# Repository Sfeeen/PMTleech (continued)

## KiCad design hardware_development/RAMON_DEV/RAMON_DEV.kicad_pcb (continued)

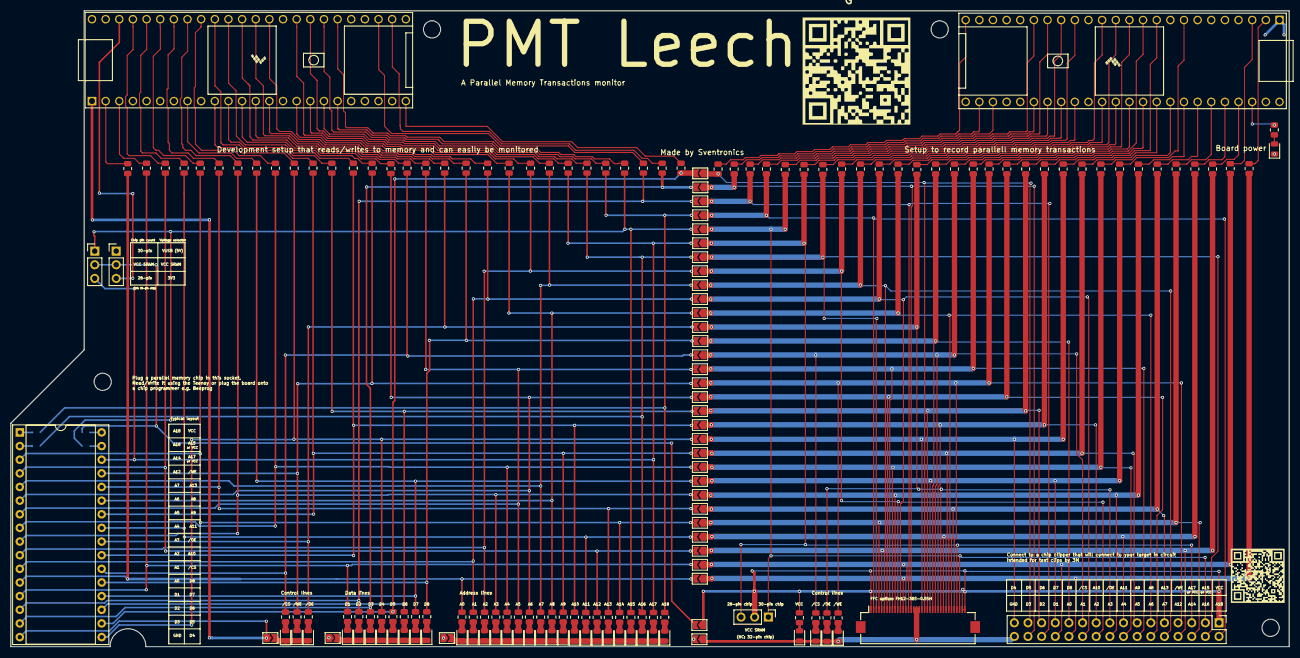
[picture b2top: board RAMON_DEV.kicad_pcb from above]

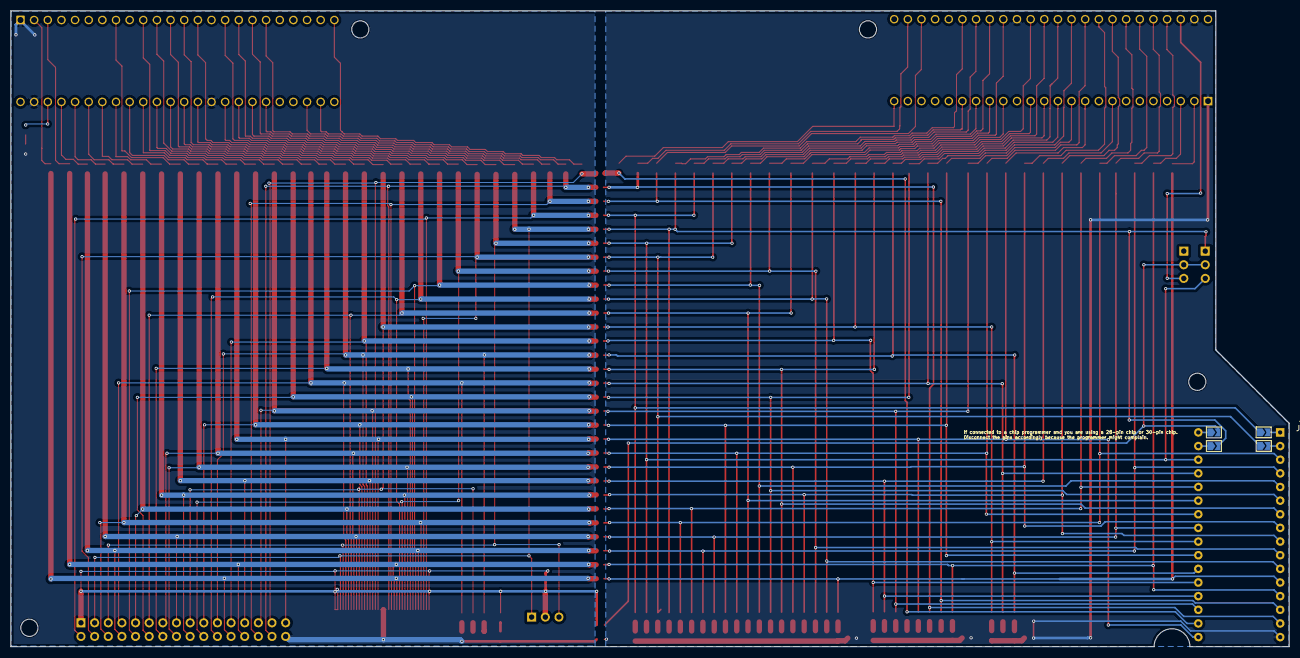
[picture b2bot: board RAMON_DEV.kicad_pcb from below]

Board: 2 copper layers, 238.0 x 118.3 mm, 181 parts (4 on the bottom side), 168 nets.

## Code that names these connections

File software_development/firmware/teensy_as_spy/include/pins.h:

#define GPIO1_3 0  
#define GPIO1_2 1  
#define GPIO2_10 6
#define GPIO2_16 8
#define GPIO2_11 9
#define GPIO2_0 10
#define GPIO2_2 11
#define GPIO2_1 12
#define GPIO1_12 24 
#define GPIO1_13 25 
#define GPIO1_30 26 
#define GPIO1_31 27 
#define GPIO2_12 32 
#define GPIO1_25 23 
#define GPIO1_24 22
#define GPIO1_27 21 
#define GPIO1_26 20 
#define GPIO1_16 19 
#define GPIO1_17 18
#define GPIO1_22 17
#define GPIO1_23 16
#define GPIO1_19 15
#define GPIO1_18 14
#define GPIO2_3 13
#define GPIO1_21 41
#define GPIO1_20 40
#define GPIO1_29 39
#define GPIO1_28 38
#define GPIO2_28 35
#define GPIO2_29 34

#define D1 GPIO1_2
#define D2 GPIO2_28
#define D3 GPIO2_29
#define D4 GPIO2_16
#define D5 GPIO2_12
#define D6 GPIO2_11
#define D7 GPIO2_10
#define D8 GPIO2_3

#define A0 GPIO1_3
#define A1 GPIO1_12
#define A2 GPIO1_13
#define A3 GPIO1_16
#define A4 GPIO1_17
#define A5 GPIO1_18
#define A6 GPIO1_19
#define A7 GPIO1_20
#define A8 GPIO1_21
#define A9 GPIO1_22
#define A10 GPIO1_23
#define A11 GPIO1_24
#define A12 GPIO1_25
#define A13 GPIO1_26
#define A14 GPIO1_27
#define A15_VCC GPIO1_28
#define A16 GPIO1_29
#define A17_VCC GPIO1_30
#define A18 GPIO1_31

#define N_CE GPIO2_2
#define N_OE GPIO2_1
#define N_WE GPIO2_0

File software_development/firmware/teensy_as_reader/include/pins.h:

#define T_GPIO1_3 0  
#define T_GPIO1_2 1  
#define T_GPIO2_10 6
#define T_GPIO2_16 8
#define T_GPIO2_11 9
#define T_GPIO2_0 10
#define T_GPIO2_2 11
#define T_GPIO2_1 12
#define T_GPIO1_12 24 
#define T_GPIO1_13 25 
#define T_GPIO1_30 26 
#define T_GPIO1_31 27 
#define T_GPIO2_12 32 
#define T_GPIO1_25 23 
#define T_GPIO1_24 22
#define T_GPIO1_27 21 
#define T_GPIO1_26 20 
#define T_GPIO1_16 19 
#define T_GPIO1_17 18
#define T_GPIO1_22 17
#define T_GPIO1_23 16
#define T_GPIO1_19 15
#define T_GPIO1_18 14
#define T_GPIO2_3 13
#define T_GPIO1_21 41
#define T_GPIO1_20 40
#define T_GPIO1_29 39
#define T_GPIO1_28 38
#define T_GPIO2_28 35
#define T_GPIO2_29 34

#define D1 T_GPIO1_2 //1
#define D2 T_GPIO2_28 //35
#define D3 T_GPIO2_29 // 34
#define D4 T_GPIO2_16 // 8
#define D5 T_GPIO2_12 // 32
#define D6 T_GPIO2_11 // 9
#define D7 T_GPIO2_10 // 6
#define D8 T_GPIO2_3 //13

#define A0 T_GPIO1_3
#define A1 T_GPIO1_12
#define A2 T_GPIO1_13
#define A3 T_GPIO1_16
#define A4 T_GPIO1_17
#define A5 T_GPIO1_18
#define A6 T_GPIO1_19
#define A7 T_GPIO1_20
#define A8 T_GPIO1_21
#define A9 T_GPIO1_22
#define A10 T_GPIO1_23
#define A11 T_GPIO1_24
#define A12 T_GPIO1_25
#define A13 T_GPIO1_26
#define A14 T_GPIO1_27
#define A15_VCC T_GPIO1_28
#define A16 T_GPIO1_29
#define A17_VCC T_GPIO1_30
#define A18 T_GPIO1_31

#define N_CE T_GPIO2_2
#define N_OE T_GPIO2_1
#define N_WE T_GPIO2_0

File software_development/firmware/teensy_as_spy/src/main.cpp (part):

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
//Special pins:
#define RUNNING_PIN 2
#define EXT_CLK_PIN 3
#define EXTRA_PIN_1 4
#define MEMORY_VCC_CONTROL 5
#define EXTRA_PIN_2 7
#define SERIAL7_RX 28
#define SERIAL7_TX 29
#define DEBUG_SPEED_CLK_ACTIVE_LED 30
#define RESET_CPU_PIN 31 
#define EXTRA_PIN_4 37
#define EXTRA_PIN_3 36
#define HIGH_SPEED_CLK_ACTIVE_LED 33

#define MEMORY_CHIP_WRITE_DELAY_MS 10 // Needs a lot time ms vs us because we drive signals through 330R resistors!! (min. value = 5ms), maybe better without leds on WE signal?
#define MEMORY_CHIP_READ_DELAY_US 10
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    return false;
  }

  pinMode(RESET_CPU_PIN, OUTPUT);
  digitalWriteFast(RESET_CPU_PIN, LOW);

  pinMode(config.cs_pin, OUTPUT);
  pinMode(config.oe_pin, OUTPUT);
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  pinMode(config.we_pin, INPUT);
  pinMode(config.cs_pin, INPUT);

  pinMode(RESET_CPU_PIN, INPUT);
}

uint8_t read_single_address(uint32_t addr){
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
  digitalWrite(DEBUG_SPEED_CLK_ACTIVE_LED, HIGH);
  digitalWrite(HIGH_SPEED_CLK_ACTIVE_LED, LOW);
  analogWriteFrequency(EXT_CLK_PIN, config.freq);
  analogWrite(EXT_CLK_PIN, 128);  // 50% duty cycle

  digitalWrite(RUNNING_PIN, HIGH);
  state = RUNNING;
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    // ✳️ XTAL mode — run EXT_CLK at specified xtal_freq
    digitalWrite(DEBUG_SPEED_CLK_ACTIVE_LED, LOW);
    digitalWrite(HIGH_SPEED_CLK_ACTIVE_LED, HIGH);
    analogWriteFrequency(EXT_CLK_PIN, config.xtal_freq);
    analogWrite(EXT_CLK_PIN, 128); // 50% duty
  } else {
    // ❌ HALT mode — disable clock
    digitalWrite(DEBUG_SPEED_CLK_ACTIVE_LED, LOW);
    digitalWrite(HIGH_SPEED_CLK_ACTIVE_LED, LOW);
    analogWrite(EXT_CLK_PIN, 0);          // Optional: reduces duty to 0%
    digitalWriteFast(EXT_CLK_PIN, LOW);   // Drive LOW
  }

  digitalWrite(RUNNING_PIN, LOW);
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

  if (we != -1) config.we_pin = line.substring(we + 3, line.indexOf(' ', we + 3)).toInt();
  if(!isvalidpin(config.we_pin))config.we_pin = EXTRA_PIN_4;
  if (oe != -1) config.oe_pin = line.substring(oe + 3, line.indexOf(' ', oe + 3)).toInt();
  if(!isvalidpin(config.oe_pin))config.oe_pin = EXTRA_PIN_3;
  if (cs != -1) config.cs_pin = line.substring(cs + 3, line.indexOf(' ', cs + 3)).toInt();
  if(!isvalidpin(config.cs_pin))config.cs_pin = EXTRA_PIN_2;
  if (freq != -1) config.freq = line.substring(freq + 5, line.indexOf(' ', freq + 5)).toInt();
  if (xtal != -1) config.xtal_freq = line.substring(xtal + 5, line.indexOf(' ', xtal + 5)).toInt();
  if (idle != -1) config.idle_behavior = line.substring(idle + 5, line.indexOf(' ', idle + 5)).toInt();
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
void perform_clock_cycles(int target_count, bool wait_for_access_flag) {
  digitalWriteFast(RUNNING_PIN, HIGH);
  pinMode(EXT_CLK_PIN, OUTPUT);
  digitalWrite(DEBUG_SPEED_CLK_ACTIVE_LED, HIGH);
  digitalWrite(HIGH_SPEED_CLK_ACTIVE_LED, LOW);

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  int count = 0;

  while (count < target_count) {
    digitalWriteFast(EXT_CLK_PIN, HIGH);
    delayMicroseconds(half_period_us);
    digitalWriteFast(EXT_CLK_PIN, LOW);
    delayMicroseconds(half_period_us);

    if (wait_for_access_flag) {
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  digitalWrite(MEMORY_VCC_CONTROL, HIGH);
  pinMode(RUNNING_PIN, OUTPUT);
  digitalWrite(RUNNING_PIN, LOW);
  pinMode(EXT_CLK_PIN, OUTPUT);
  pinMode(HIGH_SPEED_CLK_ACTIVE_LED, OUTPUT);
  pinMode(DEBUG_SPEED_CLK_ACTIVE_LED, OUTPUT);

  if (!SD.begin(BUILTIN_SDCARD)) {
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  } else if (serial_buffer == "GETCFG") {
    handle_get_config();
  } else if (serial_buffer == "RESET_CPU") {
    pinMode(RESET_CPU_PIN, OUTPUT);
    digitalWriteFast(RESET_CPU_PIN, LOW);
    delay(100);
    pinMode(RESET_CPU_PIN, INPUT);
    send_pc('X', "ACK RESET_CPU");
  } else if (serial_buffer.startsWith("STEP_")) {
      int steps = serial_buffer.substring(5).toInt();
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
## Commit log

2025-02-24 fix image
2025-04-11 backup
2025-04-12 save
2025-05-07 rendering beter performance
